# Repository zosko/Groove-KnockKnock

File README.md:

# Grove Knock-Knock Sensor for SeeedStudio

Read more at: https://www.seeedstudio.com/blog/2022/07/15/ignite-your-passion-fire-your-thoughts-develop-your-grove-sensor-with-seeed-fusion-for-a-chance-to-win-over-300usd-cash-prize%EF%BF%BC/

## Introduction

A Grove KnockKnock Sensor is a simple device that detects vibrations or shocks from knocking or tapping it. It is basically an electronic switch which normally open. When it detects any shock or vibrations, it closes.

## Components

A typical knock sensor consists of the main sensing element, which is a conductive vibrating spring, a Resistor and three Pins.
The three pins of the Knock Sensor Module are GND, +5V and Sig. The following image shows the components of a Knock Sensor Module as well as the pins on it.

## How does a Knock Sensor Work?

If you take a look at the schematic of the knock sensor, it basically consists of a switch and a resistor. The Vibrating Spring is represented as a switch here.
The output pins of the sensor is pulled HIGH with the help of a 10KΩ Pull-up resistor.
Under normal condition i.e. when there is no shock or vibrations, the output of the Knock Sensor is HIGH.
When the sensor detects any vibrations or shocks, the vibrating spring i.e. switch closes and hence the output of the sensor (at the output pin) will become LOW.

## Interfacing Knock Sensor

Now that we have seen the components of a knock sensor and how a typical knock sensor works, let us proceed with interfacing.
I have designed a simple circuit using Arduino, Knock Sensor and an LED where the LED is turned on by Arduino when the knock sensor detects any vibrations.

Also the information of the knock sensor (knock or no knock) is displayed on the Arduino IDE’s serial monitor.

## Code

````c
const int knockPin = 8;

int knockVal = HIGH;
boolean knockAlarm = false;
unsigned long prevKnockTime;
int knockAlarmTime = 100;

void setup () {
  Serial.begin(9600);  
  pinMode(knockPin, INPUT) ;
}
void loop () {
  knockVal = digitalRead(knockPin);
  
  if (knockVal == LOW) {
    prevKnockTime = millis(); 
    if (!knockAlarm) {
      Serial.println("KNOCK, KNOCK");
      knockAlarm = true;
      delay(1000);
    }
  } else {
    if( (millis() - prevKnockTime) > knockAlarmTime && knockAlarm) {
      Serial.println("No Knocks");
      knockAlarm = false;
    }
  }
}
````

## Applications

The main purpose of the Knock Sensor is to detect vibrations or shocks. Hence, the main application of such sensor can be in Door Knock System, where when a door is knocked, a notifications (like a light or a buzzer) can be activated.

## Previews

KiCad View|Seeed PCB
------|------
|

## PCB Design

For PCB design i will use services from SeeedFusion. 

Seeed Fusion PCB Assembly Service offers one-stop prototyping for PCB manufacture, PCB assembly and as a result they produce superior quality PCBs and Fast Turnkey PCBA from 7 working days. When you prototype with Seeed Fusion, they can definitely provide Free DFA and Free functional tests for you! 

Check out their website to know about their manufacturing capabilities and service.
https://www.seeedstudio.com/pcb-assembly.html

## Reasons to choose Seeed Studio
- They provide PCB services at extremely low pricing and with excellent quality.
- Their offer is structured in such a way that everyone may have these boards at a reasonable price.
- They have a highly knowledgeable crew that leads their clients to avail deals and guides them about the costs and rates of different services.
- A four-layer board with a comparable feature costs $5 for 10 pieces and is made in four days.
- SMT stencil with size (10cm x 13cm) is available for $8.00 per piece.

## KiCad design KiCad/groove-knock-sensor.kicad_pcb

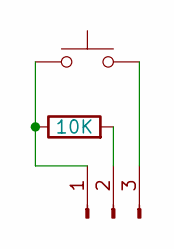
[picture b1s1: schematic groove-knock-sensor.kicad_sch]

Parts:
J1: Connector; JST_EH_B3B-EH-A_1x03_P2.50mm_Vertical
R1: 10K; R_0805_2012Metric
SW1: Vibration Switch; L_Axial_L5.3mm_D2.2mm_P10.16mm_Horizontal_Vishay_IM-1

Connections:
unnamed: J1.1, R1.1, SW1.1
unnamed: J1.2, R1.2
unnamed: J1.3, SW1.2

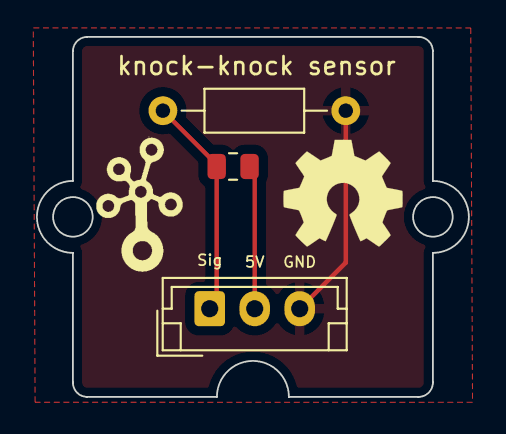
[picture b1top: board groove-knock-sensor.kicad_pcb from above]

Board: 2 copper layers, 24.0 x 20.0 mm, 4 parts (0 on the bottom side), 3 nets.

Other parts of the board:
U$3: GROVE-SILK-BIG
